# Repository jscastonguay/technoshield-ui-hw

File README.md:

# Technoshield User Interface HW

See the folling link for further details: [Technoshield Hackaday project](https://hackaday.io/project/21892-technoshield-user-interface)

## Release note

This is the description of the Technoshield HW revisions.

### Revision A

2017-05-03

The issue #1 has been fixed. This is the first revision that should be produced for students.

### Revision --
The first protoype revision.

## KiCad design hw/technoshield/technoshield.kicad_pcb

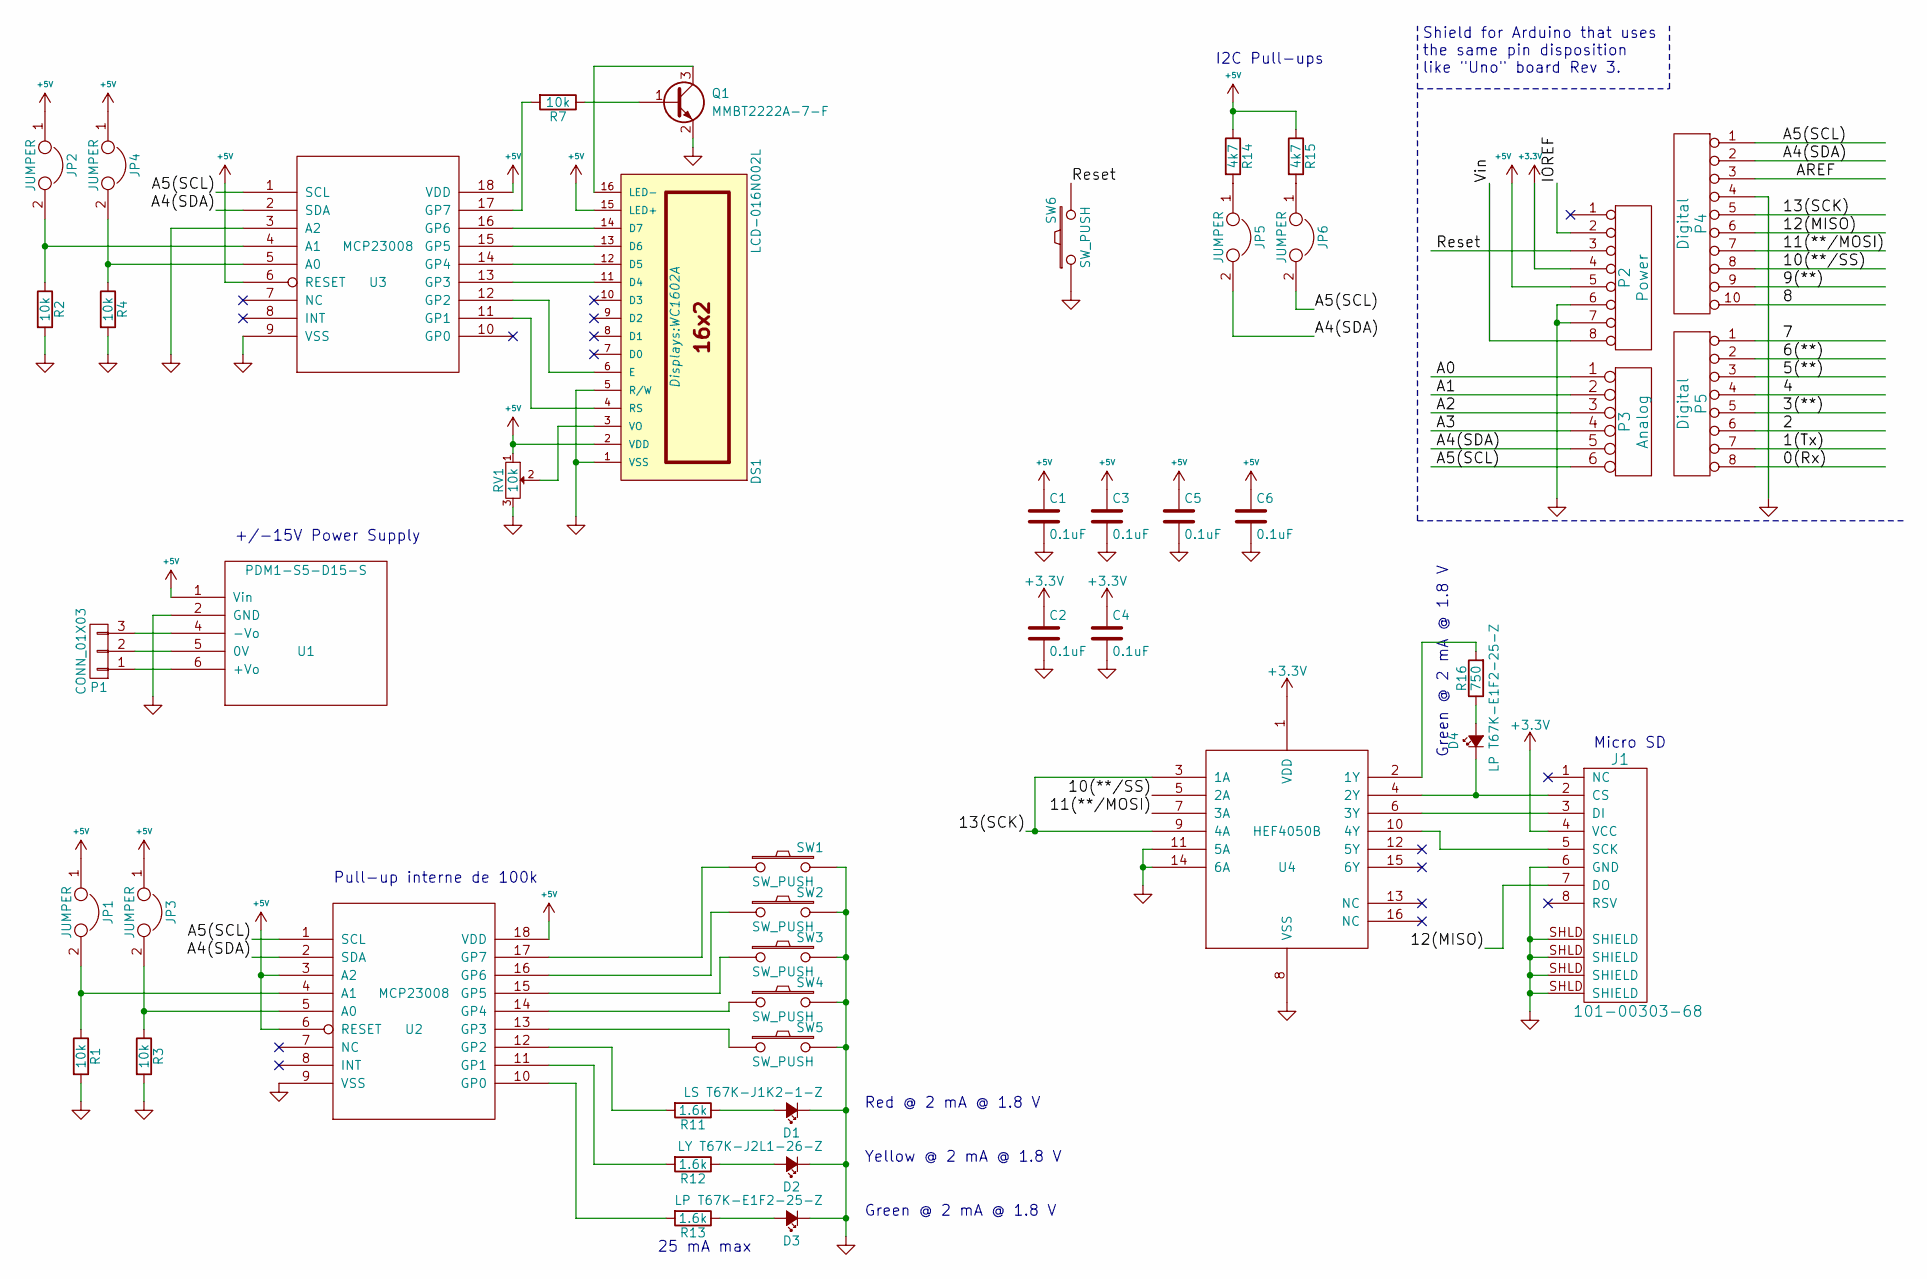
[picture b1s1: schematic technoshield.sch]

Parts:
C1, C2, C3, C4, C5, C6: 0.1uF; C_Disc_D3.0mm_W1.6mm_P2.50mm
D1: LS T67K-J1K2-1-Z; T67K
D2: LY T67K-J2L1-26-Z; T67K
D3, D4: LP T67K-E1F2-25-Z; T67K
DS1: LCD-016N002L; WC1602A
J1: 101-00303-68; MICRO_SD_HINGE_AMP
JP1, JP2, JP3, JP4, JP5, JP6: JUMPER; Pin_Header_Straight_1x02_Pitch2.54mm
P1: CONN_01X03; Pin_Header_Straight_1x03_Pitch2.54mm
P2: Power; Socket_Strip_Arduino_1x08
P3: Analog; Socket_Strip_Arduino_1x06
P4: Digital; Socket_Strip_Arduino_1x10
P5: Digital; Socket_Strip_Arduino_1x08
Q1: MMBT2222A-7-F; SOT-23
R1, R2, R3, R4, R7: 10k; R_Axial_DIN0204_L3.6mm_D1.6mm_P7.62mm_Horizontal
R11, R12, R13: 1.6k; R_Axial_DIN0204_L3.6mm_D1.6mm_P7.62mm_Horizontal
R14, R15: 4k7; R_Axial_DIN0204_L3.6mm_D1.6mm_P7.62mm_Horizontal
R16: 750; R_Axial_DIN0204_L3.6mm_D1.6mm_P7.62mm_Horizontal
RV1: 10k; POTENTIOMETRE_BOURNS_3319P
SW1, SW2, SW3, SW4, SW5, SW6: SW_PUSH; smt_btn
U1: PDM1-S5-D15-S; PDM1-S
U2, U3: MCP23008; DIP-18_W7.62mm_LongPads
U4: HEF4050B; SO16-3_9mm

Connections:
+3V3: C2.1, C4.1, J1.4 (VCC), P2.4, U4.1 (VDD)
+5V: C1.1, C3.1, C5.1, C6.1, DS1.2 (VDD), DS1.15 (LED+), JP1.1, JP2.1, JP3.1, JP4.1, P2.5, R14.1, R15.1, RV1.1, U1.1 (Vin), U2.3 (A2), U2.6 (RESET), U2.18 (VDD), U3.6 (RESET), U3.18 (VDD)
/0(Rx): P5.8
/1(Tx): P5.7
/2: P5.6
/3(**): P5.5
/4: P5.4
/5(**): P5.3
/6(**): P5.2
/7: P5.1
/8: P4.10
/9(**): P4.9
/10(**/SS): P4.8, U4.5 (2A)
/11(**/MOSI): P4.7, U4.7 (3A)
/12(MISO): J1.7 (DO), P4.6
/13(SCK): P4.5, U4.3 (1A), U4.9 (4A)
/A0: P3.1
/A1: P3.2
/A2: P3.3
/A3: P3.4
/A4(SDA): JP5.2, P3.5, P4.2, U2.2 (SDA), U3.2 (SDA)
/A5(SCL): JP6.2, P3.6, P4.1, U2.1 (SCL), U3.1 (SCL)
/AREF: P4.3
/IOREF: P2.2
/Reset: P2.3, SW6.2
/Vin: P2.8
GND: C1.2, C2.2, C3.2, C4.2, C5.2, C6.2, D1.1 (K), D2.1 (K), D3.1 (K), DS1.1 (VSS), DS1.5 (R/W), J1.6 (GND), J1.SHLD (SHIELD), P2.6, P2.7, P4.4, Q1.2 (E), R1.2, R2.2, R3.2, R4.2, RV1.3, SW1.2, SW2.2, SW3.2, SW4.2, SW5.2, SW6.1, U1.2 (GND), U2.9 (VSS), U3.3 (A2), U3.9 (VSS), U4.8 (VSS), U4.11 (5A), U4.14 (6A)
unnamed: D1.2 (A), R11.1
unnamed: D2.2 (A), R12.1
unnamed: D3.2 (A), R13.1
unnamed: D4.1 (K), J1.2 (CS), U4.4 (2Y)
unnamed: D4.2 (A), R16.1
unnamed: DS1.3 (VO), RV1.2
unnamed: DS1.4 (RS), U3.11 (GP1)
unnamed: DS1.6 (E), U3.12 (GP2)
unnamed: DS1.11 (D4), U3.13 (GP3)
unnamed: DS1.12 (D5), U3.14 (GP4)
unnamed: DS1.13 (D6), U3.15 (GP5)
unnamed: DS1.14 (D7), U3.16 (GP6)
unnamed: DS1.16 (LED-), Q1.3 (C)
unnamed: J1.3 (DI), U4.6 (3Y)
unnamed: J1.5 (SCK), U4.10 (4Y)
unnamed: JP1.2, R1.1, U2.4 (A1)
unnamed: JP2.2, R2.1, U3.4 (A1)
unnamed: JP3.2, R3.1, U2.5 (A0)
unnamed: JP4.2, R4.1, U3.5 (A0)
unnamed: JP5.1, R14.2
unnamed: JP6.1, R15.2
unnamed: P1.1, U1.6 (+Vo)
unnamed: P1.2, U1.5 (0V)
unnamed: P1.3, U1.4 (-Vo)
unnamed: Q1.1 (B), R7.1
unnamed: R7.2, U3.17 (GP7)
unnamed: R11.2, U2.12 (GP2)
unnamed: R12.2, U2.11 (GP1)
unnamed: R13.2, U2.10 (GP0)
unnamed: R16.2, U4.2 (1Y)
unnamed: SW1.1, U2.17 (GP7)
unnamed: SW2.1, U2.16 (GP6)
unnamed: SW3.1, U2.15 (GP5)
unnamed: SW4.1, U2.14 (GP4)
unnamed: SW5.1, U2.13 (GP3)

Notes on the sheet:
Shield for Arduino that uses the same pin disposition like "Uno" board Rev 3.
I2C Pull-ups
Pull-up interne de 100k
25 mA max
+/-15V Power Supply
Red @ 2 mA @ 1.8 V
Yellow @ 2 mA @ 1.8 V
Green @ 2 mA @ 1.8 V
Micro SD

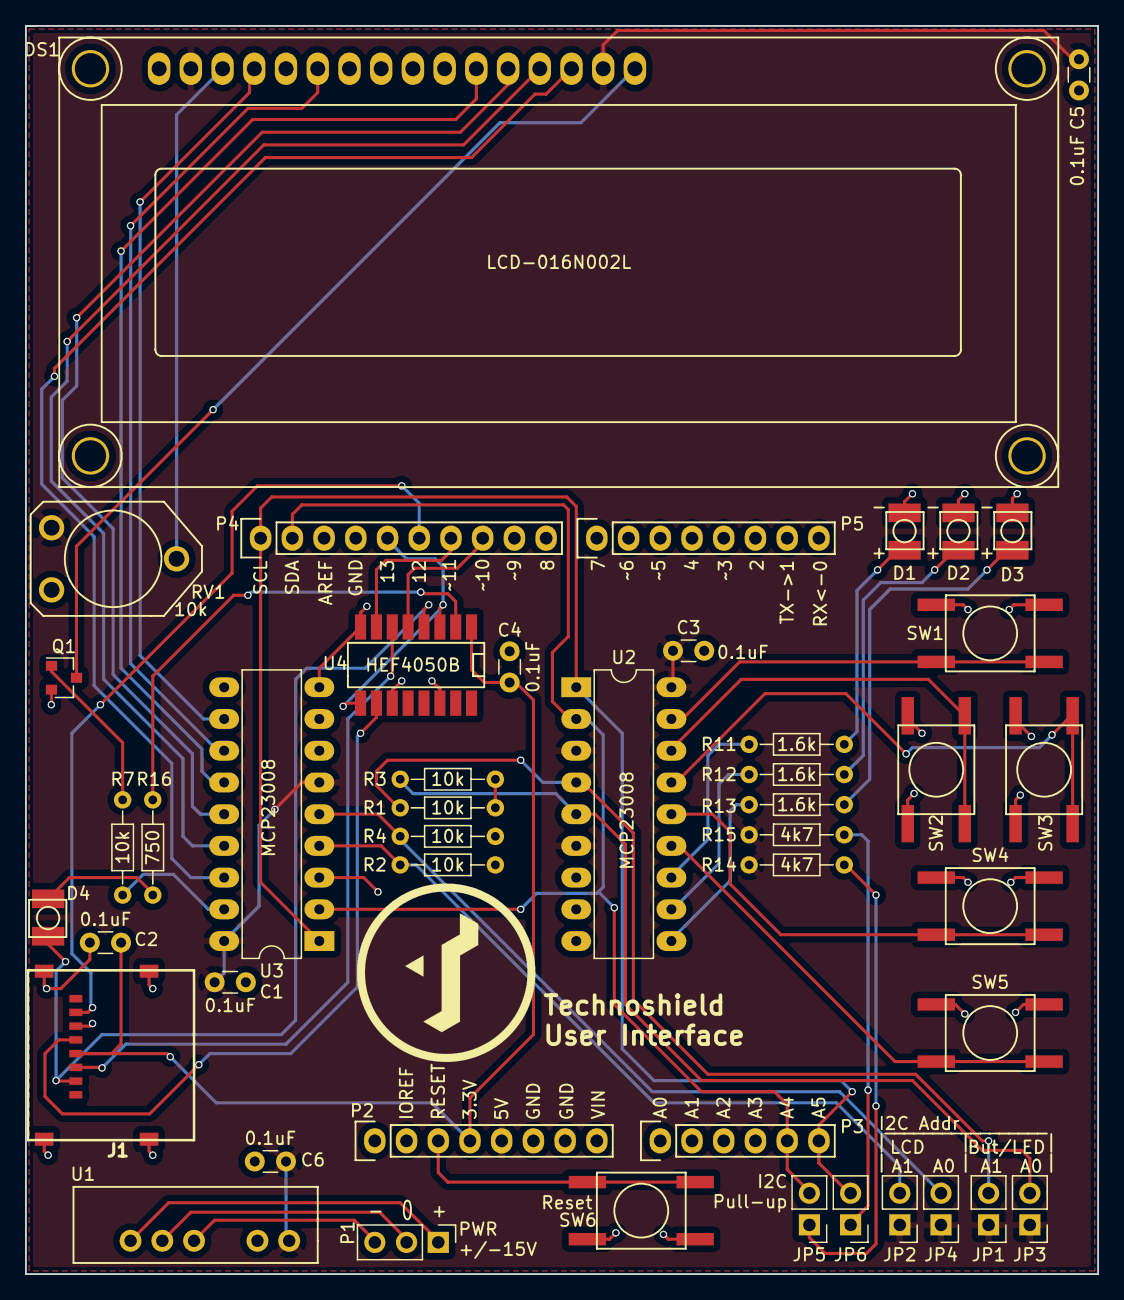
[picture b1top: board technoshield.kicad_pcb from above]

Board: 2 copper layers, 85.9 x 99.9 mm, 46 parts (0 on the bottom side), 45 nets.

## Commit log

2016-11-15 add README
2016-11-25 Durant le développement.
2016-12-09 During developpment.
2017-01-22 During dev.
2017-02-03 During dev PCB.
2017-02-04 Dev of Rev -- almost finish.
2017-02-09 Gerber done.
2017-04-26 Add to github.
2017-05-01 Issue #1: Problems found in prototype rev-- Problem with USB and component contact fixed.
2017-05-02 Add logo.
2017-05-03 Issue #1 fixed.
2017-05-22 BOM added.
2017-06-13 "Notice de montage Technoshield.docx" added.

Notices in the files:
hw/technoshield/technoshield.kicad_pcb:
Released under the Creative Commons Attribution Share-Alike 4.0 License
Copyright 2017 Jean-Sébastien Castonguay
hw/technoshield/technoshield.sch:
https://creativecommons.org/licenses/by-sa/4.0
